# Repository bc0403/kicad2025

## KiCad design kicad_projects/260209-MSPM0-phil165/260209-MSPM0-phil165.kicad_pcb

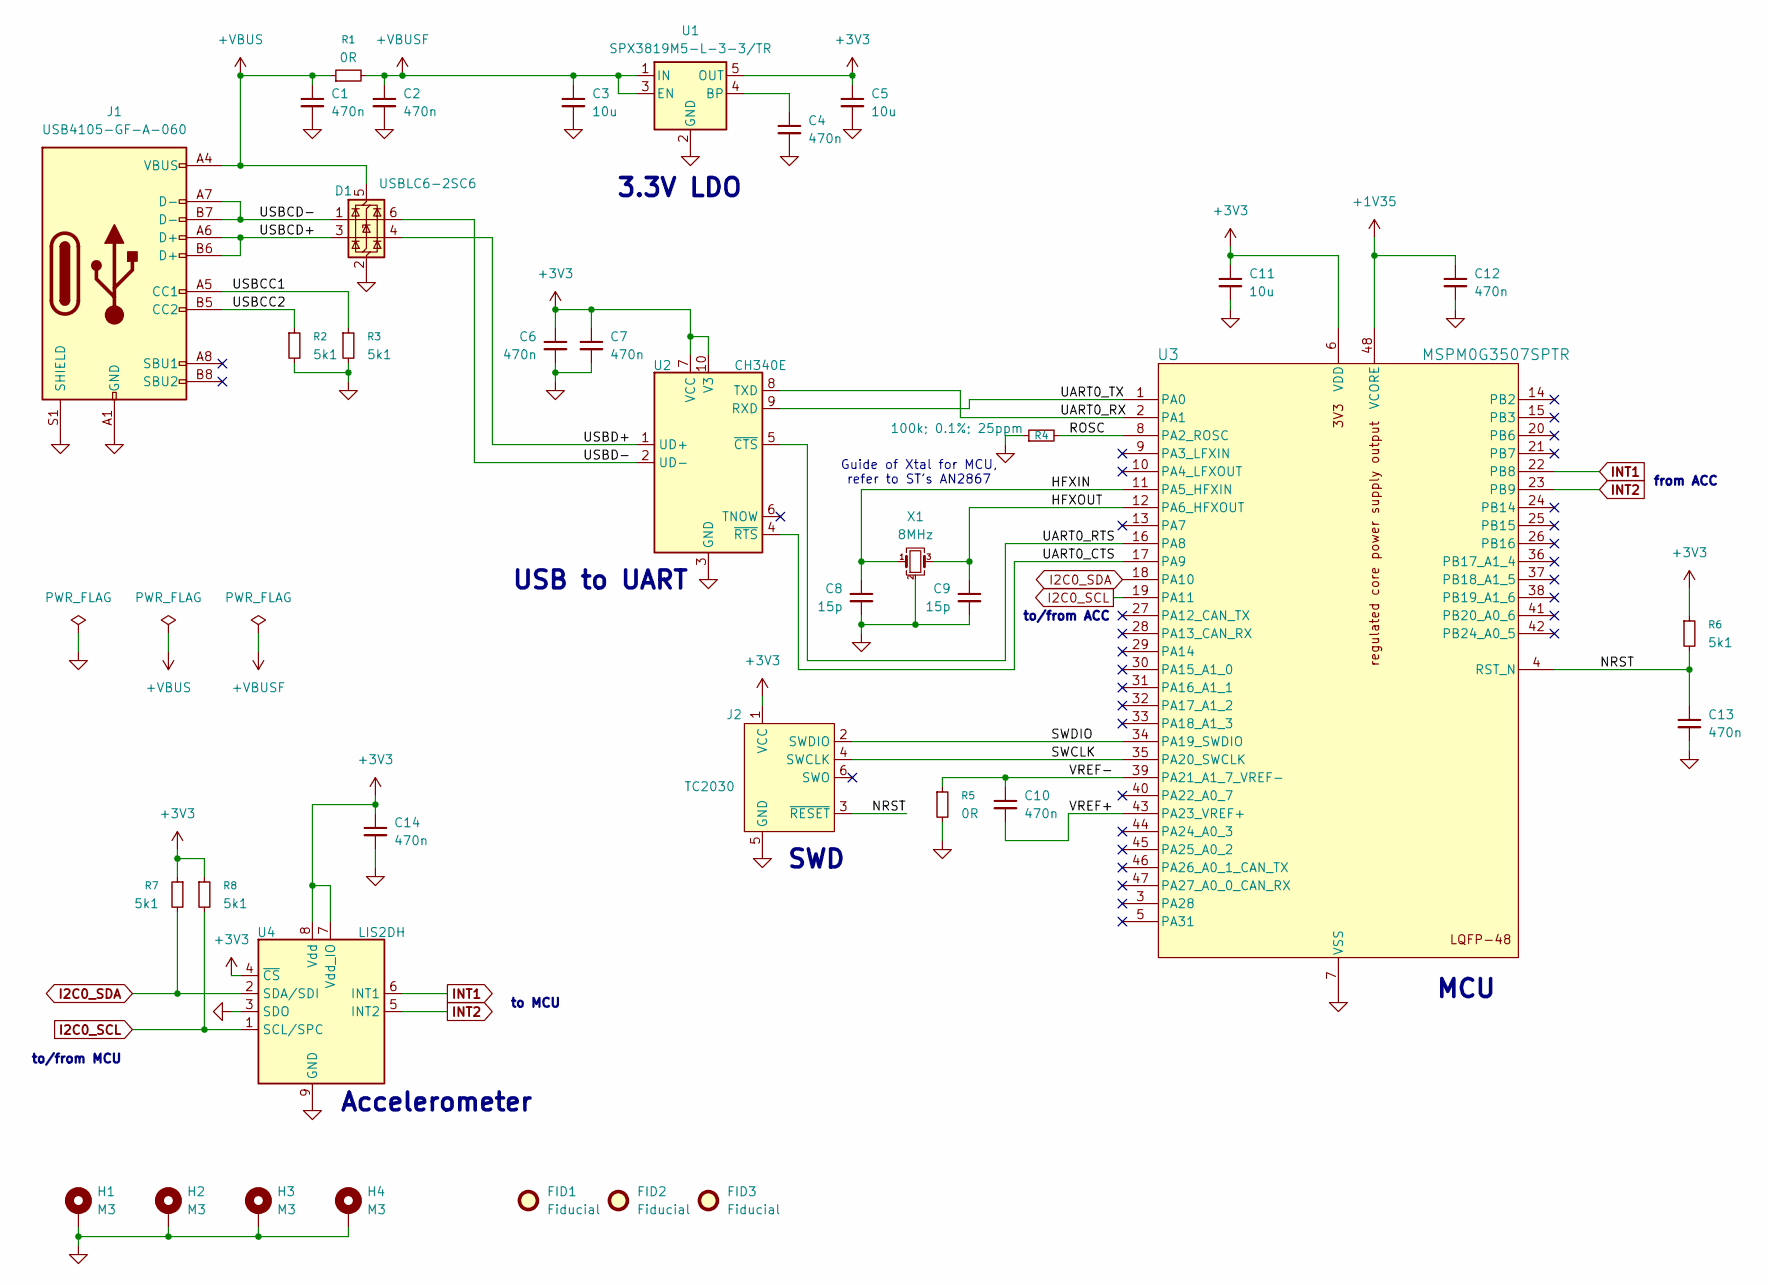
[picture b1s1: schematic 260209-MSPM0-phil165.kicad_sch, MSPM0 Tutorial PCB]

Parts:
C1, C2, C4, C6, C7, C10, C12, C13, C14: 470n; C_0603_1608Metric; MPN CL10B474KA8NNNC; Digikey 1276-2083-2-ND
C3, C5, C11: 10u; C_0805_2012Metric; MPN CL21A106KAYNNNE; Digikey 1276-2891-2-ND
C8, C9: 15p; C_0603_1608Metric; MPN CL10C150JB8NNNC; Digikey 1276-1296-2-ND
D1: USBLC6-2SC6; SOT-23-6; MPN USBLC6-2SC6; Digikey 497-5235-2-ND
FID1, FID2, FID3: Fiducial; Fiducial_1mm_Mask2mm
H1, H2, H3, H4: M3; MountingHole_3.2mm_M3_Pad_Via
J1: USB4105-GF-A-060; USB_C_Receptacle_GCT_USB4105-xx-A_16P_TopMnt_Horizontal; MPN USB4105-GF-A-060; Digikey CONN RCP USB2.0 TYP C 16P SMD RA
J2: TC2030; Tag-Connect_TC2030-IDC-FP_2x03_P1.27mm_Vertical
R1, R5: 0R; R_0603_1608Metric; MPN RC0603FR-070RL; Digikey 311-0.0HRTR-ND
R2, R3, R6, R7, R8: 5k1; R_0603_1608Metric; MPN RC0603FR-075K1L; Digikey 311-5.10KHRTR-ND
R4: 100k; 0.1%; 25ppm; R_0603_1608Metric; MPN RT0603BRD07100KL; Digikey YAG1235TR-ND
U1: SPX3819M5-L-3-3/TR; SOT-23-5; MPN SPX3819M5-L-3-3/TR; Digikey 1016-1873-2-ND
U2: CH340E; MSOP-10_3x3mm_P0.5mm; MPN CH340E; LCSC C99652
U3: MSPM0G3507SPTR; LQFP-48_7x7mm_P0.5mm; MPN MSPM0G3507SPTR; Digikey 296-MSPM0G3507SPTR-ND
U4: LIS2DH; LGA-14_2x2mm_P0.35mm_LayoutBorder3x4y; MPN LIS2DHTR; Digikey 497-13795-2-ND
X1: 8MHz; Crystal_SMD_3225-4Pin_3.2x2.5mm; MPN ECS-80-12-33-JGN-TR; Digikey 50-ECS-80-12-33-JGN-TR-ND

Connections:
+1V35: C12.1, U3.48 (VCORE)
+3V3: C5.1, C6.1, C7.1, C11.1, C14.1, J2.1 (VCC), R6.1, R7.1, R8.1, U1.5 (OUT), U2.7 (VCC), U2.10 (V3), U3.6 (VDD), U4.4 (~CS), U4.7 (Vdd_IO), U4.8 (Vdd)
+VBUS: C1.1, D1.5 (VBUS), J1.A4 (VBUS), J1.A9 (VBUS), J1.B4 (VBUS), J1.B9 (VBUS), R1.1
+VBUSF: C2.1, C3.1, R1.2, U1.1 (IN), U1.3 (EN)
/HFXIN: C8.1, U3.11 (PA5_HFXIN), X1.1
/HFXOUT: C9.1, U3.12 (PA6_HFXOUT), X1.3
/NRST: C13.1, J2.3 (~RESET), R6.2, U3.4 (RST_N)
/ROSC: R4.2, U3.8 (PA2_ROSC)
/SWCLK: J2.4 (SWCLK), U3.35 (PA20_SWCLK)
/SWDIO: J2.2 (SWDIO), U3.34 (PA19_SWDIO)
/UART0_CTS: U2.4 (~RTS), U3.17 (PA9)
/UART0_RTS: U2.5 (~CTS), U3.16 (PA8)
/UART0_RX: U2.8 (TXD), U3.2 (PA1)
/UART0_TX: U2.9 (RXD), U3.1 (PA0)
/USBCC1: J1.A5 (CC1), R3.1
/USBCC2: J1.B5 (CC2), R2.1
/USBCD+: D1.3 (I/O2), J1.A6 (D+), J1.B6 (D+)
/USBCD-: D1.1 (I/O1), J1.A7 (D-), J1.B7 (D-)
/USBD+: D1.4 (I/O2), U2.1 (UD+)
/USBD-: D1.6 (I/O1), U2.2 (UD-)
/VREF+: C10.2, U3.43 (PA23_VREF+)
/VREF-: C10.1, R5.1, U3.39 (PA21_A1_7_VREF-)
GND: C1.2, C2.2, C3.2, C4.2, C5.2, C6.2, C7.2, C8.2, C9.2, C11.2, C12.2, C13.2, C14.2, D1.2 (GND), H1.1, H2.1, H3.1, H4.1, J1.A1 (GND), J1.A12 (GND), J1.B1 (GND), J1.B12 (GND), J1.S1 (SHIELD), J2.5 (GND), R2.2, R3.2, R4.1, R5.2, U1.2 (GND), U2.3 (GND), U3.7 (VSS), U4.3 (SDO), U4.9 (GND), U4.10 (GND), U4.11 (GND), U4.12 (GND), U4.13 (GND), U4.14 (GND), X1.2 (G), X1.4 (G)
I2C0_SCL: R8.2, U3.19 (PA11), U4.1 (SCL/SPC)
I2C0_SDA: R7.2, U3.18 (PA10), U4.2 (SDA/SDI)
INT1: U3.22 (PB8), U4.6 (INT1)
INT2: U3.23 (PB9), U4.5 (INT2)
unnamed: C4.1, U1.4 (BP)

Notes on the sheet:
to/from MCU
3.3V LDO
to MCU
USB to UART
Accelerometer
to/from ACC
Guide of Xtal for MCU, refer to ST's AN2867
SWD
from ACC
MCU

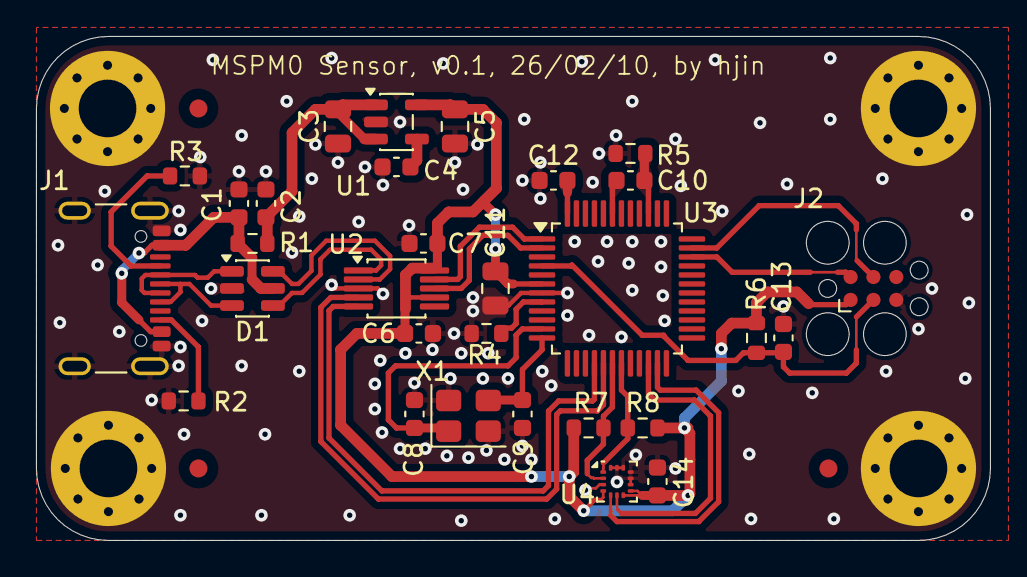
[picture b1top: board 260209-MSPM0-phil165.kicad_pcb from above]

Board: 2 copper layers, 53.0 x 28.0 mm, 37 parts (0 on the bottom side), 28 nets.

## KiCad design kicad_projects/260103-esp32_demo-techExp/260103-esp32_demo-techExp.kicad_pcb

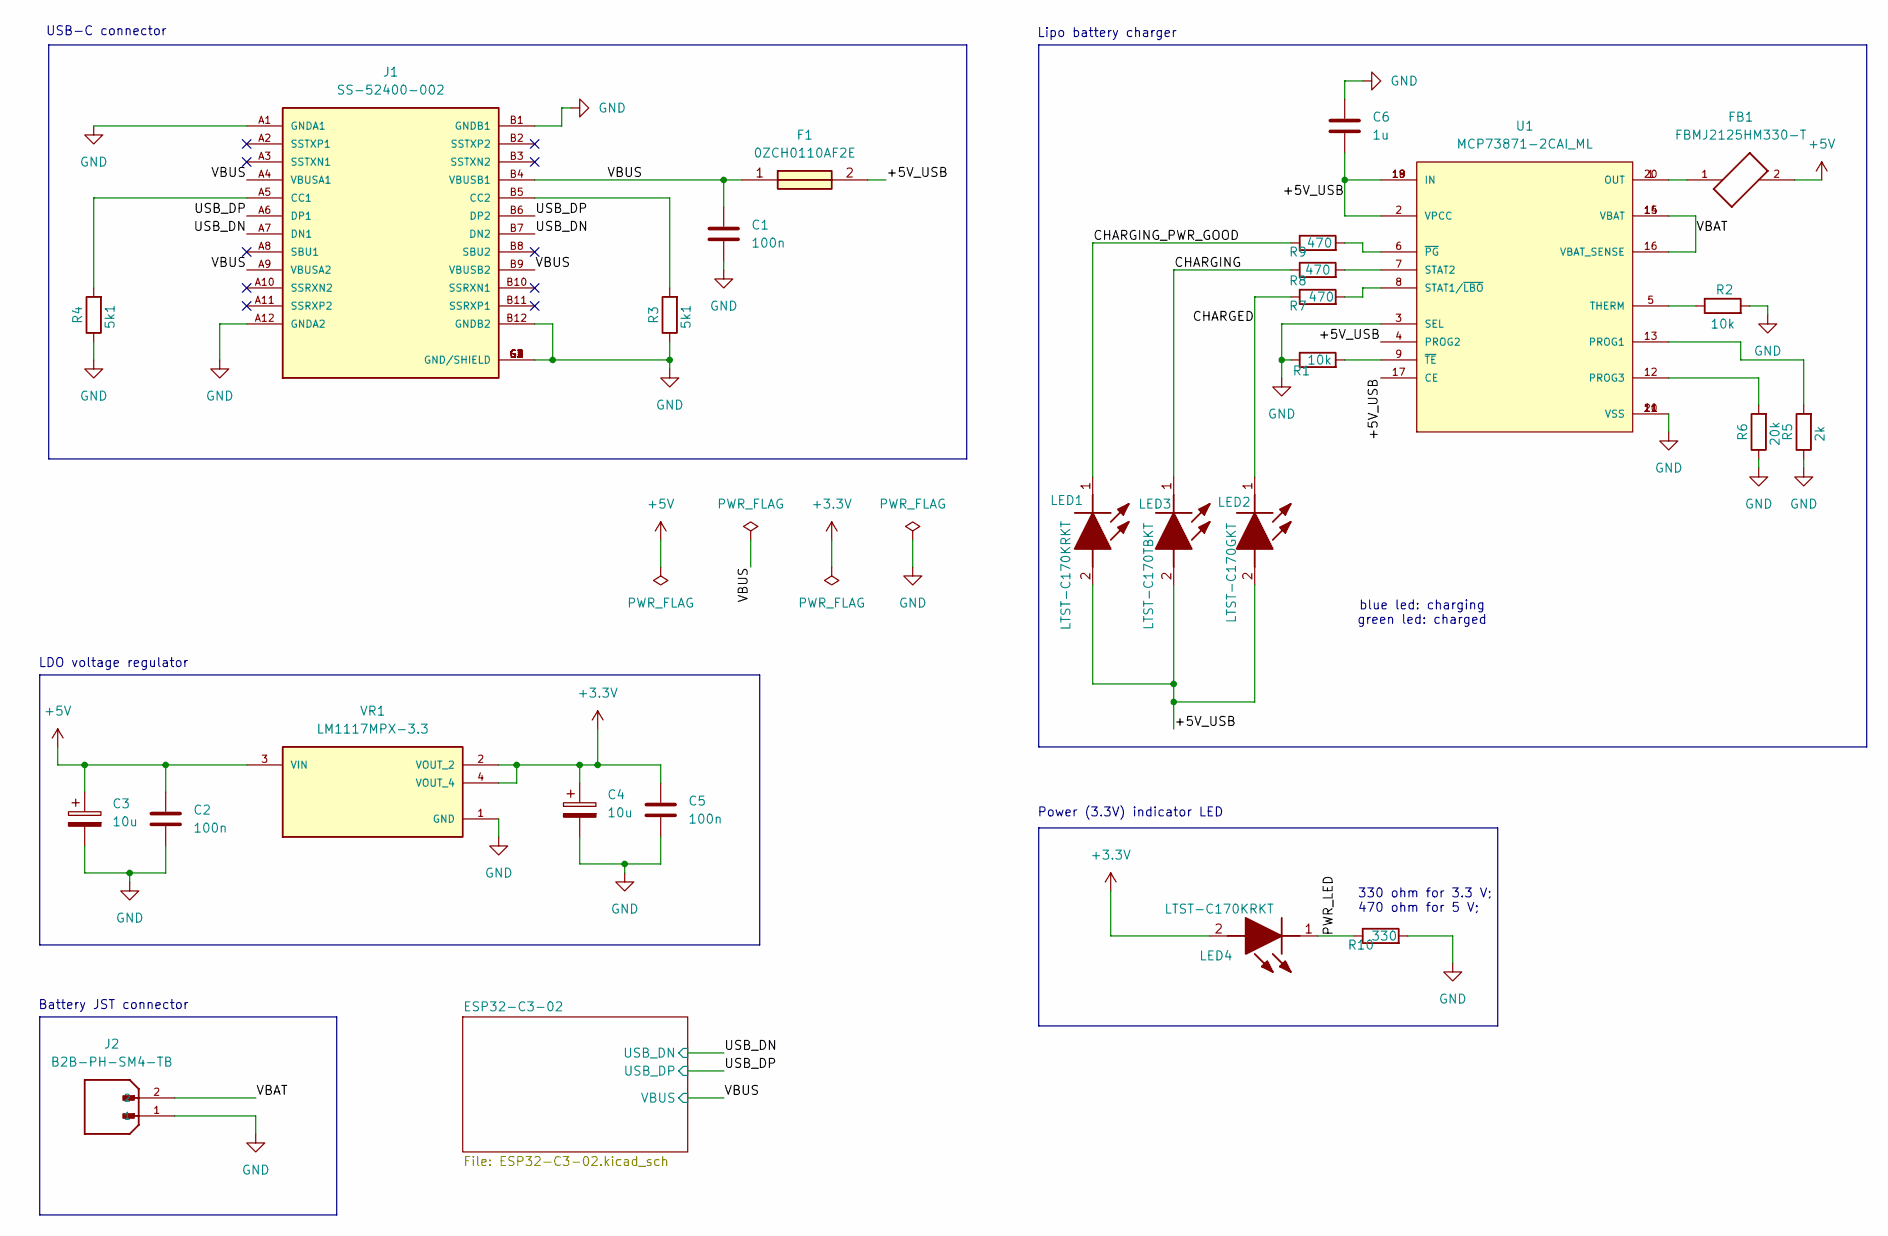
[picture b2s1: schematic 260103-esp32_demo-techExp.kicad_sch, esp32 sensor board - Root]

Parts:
C1, C2, C5: 100n; C_0805_2012Metric
C3, C4: 10u; T491A
C6: 1u; C_0805_2012Metric
F1: 0ZCH0110AF2E; FUSC3226X100N; Manufacturer_Part_Number 0ZCH0110AF2E
FB1: FBMJ2125HM330-T; BEADC2012X105N
J1: SS-52400-002; BELFUSE_SS-52400-002; PARTREV A0
J2: B2B-PH-SM4-TB; JST_B2B-PH-SM4-TB; PARTREV N/A
LED1, LED4: LTST-C170KRKT; LEDC2012X120N; Manufacturer_Part_Number LTST-C170KRKT; Mouser Part Number 859-LTST-C170KRKT
LED2: LTST-C170GKT; LEDC2012X120N; Manufacturer_Part_Number LTST-C170GKT; Mouser Part Number 859-LTST-C170GKT
LED3: LTST-C170TBKT; LEDC2012X120N; Manufacturer_Part_Number LTST-C170TBKT; Mouser Part Number 859-LTST-C170TBKT
R1, R2: 10k; R_0805_2012Metric
R3, R4: 5k1; R_0805_2012Metric
R5: 2k; R_0805_2012Metric
R6: 20k; R_0805_2012Metric
R7, R8, R9: 470; R_0805_2012Metric
R10: 330; R_0805_2012Metric
U1: MCP73871-2CAI_ML; QFN50P400X400X100-21N; PARTREV D
VR1: LM1117MPX-3.3; VREG_LM1117MPX-3.3

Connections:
+3.3V: C4.1, C5.1, LED4.2 (A), VR1.2 (VOUT_2), VR1.4 (VOUT_4); also elsewhere on the board
+5V: C2.1, C3.1, FB1.2, VR1.3 (VIN)
/+5V_USB: C6.2, F1.2, LED1.2 (A), LED2.2 (A), LED3.2 (A), U1.2 (VPCC), U1.4 (PROG2), U1.17 (CE), U1.18 (IN), U1.19 (IN)
/CHARGED: LED2.1 (K), R7.1
/CHARGING: LED3.1 (K), R8.1
/CHARGING_PWR_GOOD: LED1.1 (K), R9.1
/PWR_LED: LED4.1 (K), R10.1
/USB_DN: J1.A7 (DN1), J1.B7 (DN2); also elsewhere on the board
/USB_DP: J1.A6 (DP1), J1.B6 (DP2); also elsewhere on the board
/VBAT: J2.2, U1.14 (VBAT), U1.15 (VBAT), U1.16 (VBAT_SENSE)
/VBUS: C1.1, F1.1, J1.A4 (VBUSA1), J1.A9 (VBUSA2), J1.B4 (VBUSB1), J1.B9 (VBUSB2); also elsewhere on the board
GND: C1.2, C2.2, C3.2, C4.2, C5.2, C6.1, J1.A1 (GNDA1), J1.A12 (GNDA2), J1.B1 (GNDB1), J1.B12 (GNDB2), J1.G1 (GND/SHIELD), J1.G2 (GND/SHIELD), J1.G3 (GND/SHIELD), J1.G4 (GND/SHIELD), J1.S1 (GND/SHIELD), J1.S2 (GND/SHIELD), J1.S3 (GND/SHIELD), J1.S4 (GND/SHIELD), J2.1, R1.1, R2.2, R3.1, R4.1, R5.1, R6.1, R10.2, U1.3 (SEL), U1.10 (VSS), U1.11 (VSS), U1.21 (VSS), VR1.1 (GND); also elsewhere on the board
unnamed: FB1.1, U1.1 (OUT), U1.20 (OUT)
unnamed: J1.A5 (CC1), R4.2
unnamed: J1.B5 (CC2), R3.2
unnamed: R5.2, U1.13 (PROG1)
unnamed: R6.2, U1.12 (PROG3)
unnamed: R7.2, U1.8 (STAT1/~LBO)
unnamed: R8.2, U1.7 (STAT2)
unnamed: R2.1, U1.5 (THERM)
unnamed: R9.2, U1.6 (~PG)
unnamed: R1.2, U1.9 (~TE)

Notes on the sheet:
Lipo battery charger
330 ohm for 3.3 V; 470 ohm for 5 V;
Battery JST connector
blue led: charging green led: charged
LDO voltage regulator
Power (3.3V) indicator LED
USB-C connector

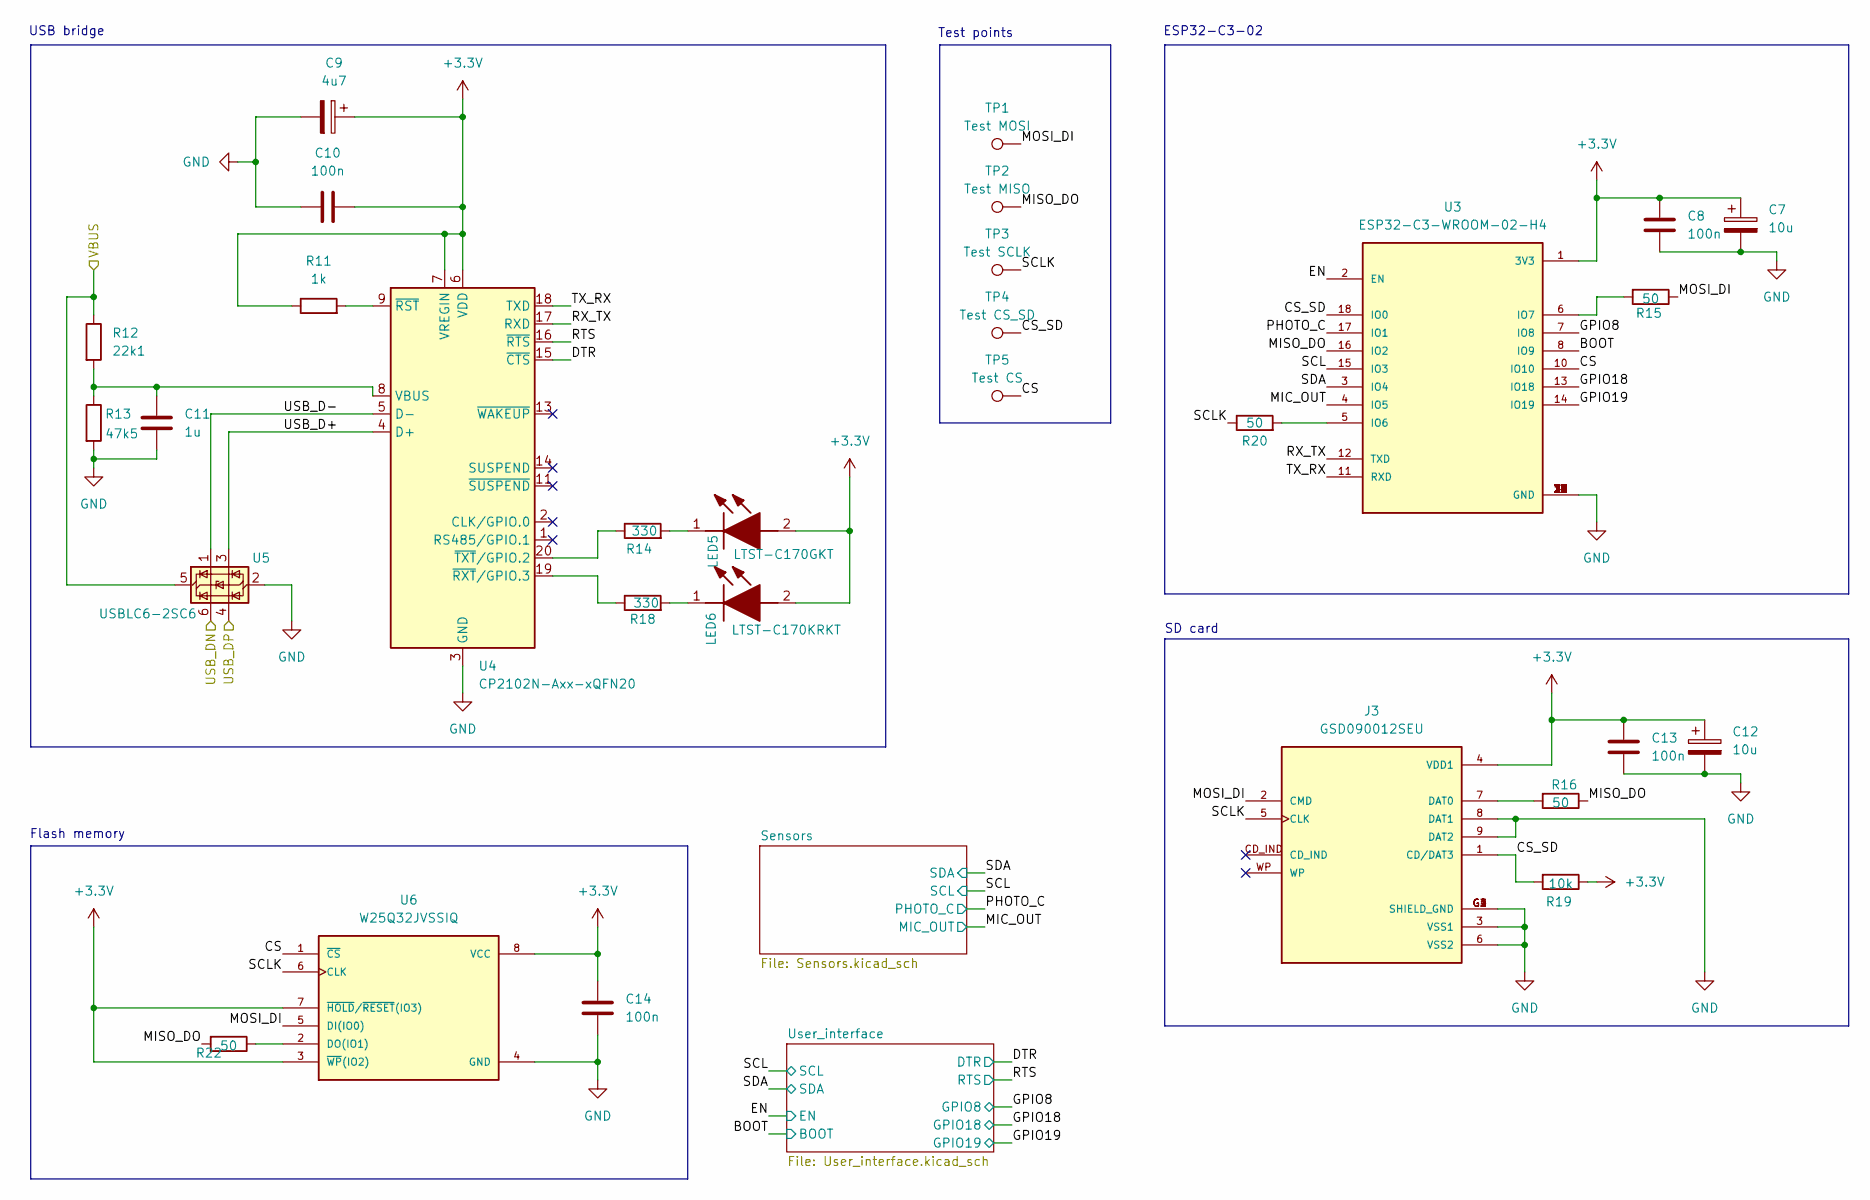
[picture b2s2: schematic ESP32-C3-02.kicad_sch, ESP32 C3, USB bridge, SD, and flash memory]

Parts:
C7, C12: 10u; T491A
C8, C10, C13, C14: 100n; C_0805_2012Metric
C9: 4u7; T491A
C11: 1u; C_0805_2012Metric
J3: GSD090012SEU; AMPHENOL_GSD090012SEU; PARTREV E
LED5: LTST-C170GKT; LEDC2012X120N; Manufacturer_Part_Number LTST-C170GKT; Mouser Part Number 859-LTST-C170GKT
LED6: LTST-C170KRKT; LEDC2012X120N; Manufacturer_Part_Number LTST-C170KRKT; Mouser Part Number 859-LTST-C170KRKT
R11: 1k; R_0805_2012Metric
R12: 22k1; R_0805_2012Metric
R13: 47k5; R_0805_2012Metric
R14, R18: 330; R_0805_2012Metric
R15, R16, R20, R22: 50; R_0805_2012Metric
R19: 10k; R_0805_2012Metric
TP1: Test MOSI; TestPoint_Pad_D1.0mm
TP2: Test MISO; TestPoint_Pad_D1.0mm
TP3: Test SCLK; TestPoint_Pad_D1.0mm
TP4: Test CS_SD; TestPoint_Pad_D1.0mm
TP5: Test CS; TestPoint_Pad_D1.0mm
U3: ESP32-C3-WROOM-02-H4; MODULE_ESP32-C3-WROOM-02-H4
U4: CP2102N-Axx-xQFN20; SiliconLabs_QFN-20-1EP_3x3mm_P0.5mm_EP1.8x1.8mm
U5: USBLC6-2SC6; SOT-23-6
U6: W25Q32JVSSIQ; SOIC127P790X216-8N; M_PART_NUMBER W25QXX

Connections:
+3.3V: C7.1, C8.1, C9.1, C10.2, C12.1, C13.1, C14.1, J3.4 (VDD1), LED5.2 (A), LED6.2 (A), R11.1, R19.1, U3.1 (3V3), U4.6 (VDD), U4.7 (VREGIN), U6.3 (~WP(IO2)), U6.7 (~HOLD/~RESET(IO3)), U6.8 (VCC); also elsewhere on the board
/ESP32-C3-02/BOOT: U3.8 (IO9); also elsewhere on the board
/ESP32-C3-02/CS: TP5.1, U3.10 (IO10), U6.1 (~CS)
/ESP32-C3-02/CS_SD: J3.1 (CD/DAT3), R19.2, TP4.1, U3.18 (IO0)
/ESP32-C3-02/DTR: U4.15 (~CTS); also elsewhere on the board
/ESP32-C3-02/EN: U3.2 (EN); also elsewhere on the board
/ESP32-C3-02/GPIO8: U3.7 (IO8); also elsewhere on the board
/ESP32-C3-02/GPIO18: U3.13 (IO18); also elsewhere on the board
/ESP32-C3-02/GPIO19: U3.14 (IO19); also elsewhere on the board
/ESP32-C3-02/MIC_OUT: U3.4 (IO5); also elsewhere on the board
/ESP32-C3-02/MISO_DO: R16.1, R22.2, TP2.1, U3.16 (IO2)
/ESP32-C3-02/MOSI_DI: J3.2 (CMD), R15.1, TP1.1, U6.5 (DI(IO0))
/ESP32-C3-02/PHOTO_C: U3.17 (IO1); also elsewhere on the board
/ESP32-C3-02/RTS: U4.16 (~RTS); also elsewhere on the board
/ESP32-C3-02/RX_TX: U3.12 (TXD), U4.17 (RXD)
/ESP32-C3-02/SCL: U3.15 (IO3); also elsewhere on the board
/ESP32-C3-02/SCLK: J3.5 (CLK), R20.1, TP3.1, U6.6 (CLK)
/ESP32-C3-02/SDA: U3.3 (IO4); also elsewhere on the board
/ESP32-C3-02/TX_RX: U3.11 (RXD), U4.18 (TXD)
/ESP32-C3-02/USB_D+: U4.4 (D+), U5.3 (I/O2)
/ESP32-C3-02/USB_D-: U4.5 (D-), U5.1 (I/O1)
/USB_DN: U5.6 (I/O1); also elsewhere on the board
/USB_DP: U5.4 (I/O2); also elsewhere on the board
/VBUS: R12.1, U5.5 (VBUS); also elsewhere on the board
GND: C7.2, C8.2, C9.2, C10.1, C11.2, C12.2, C13.2, C14.2, J3.3 (VSS1), J3.6 (VSS2), J3.8 (DAT1), J3.9 (DAT2), J3.G1 (SHIELD_GND), J3.G2 (SHIELD_GND), J3.G3 (SHIELD_GND), J3.G4 (SHIELD_GND), R13.2, U3.9 (GND), U3.19 (GND), U3.20 (GND), U3.21 (GND), U3.22 (GND), U3.23 (GND), U3.24 (GND), U3.25 (GND), U3.26 (GND), U3.27 (GND), U3.28 (GND), U3.29 (GND), U3.30 (GND), U3.31 (GND), U3.32 (GND), U3.33 (GND), U3.34 (GND), U3.35 (GND), U3.36 (GND), U3.37 (GND), U3.38 (GND), U3.39 (GND), U4.3 (GND), U4.12 (GND), U4.21 (GND), U5.2 (GND), U6.4 (GND); also elsewhere on the board
unnamed: J3.7 (DAT0), R16.2
unnamed: LED5.1 (K), R14.2
unnamed: LED6.1 (K), R18.2
unnamed: R20.2, U3.5 (IO6)
unnamed: R15.2, U3.6 (IO7)
unnamed: C11.1, R12.2, R13.1, U4.8 (VBUS)
unnamed: R11.2, U4.9 (~RST)
unnamed: R18.1, U4.19 (~RXT/GPIO.3)
unnamed: R14.1, U4.20 (~TXT/GPIO.2)
unnamed: R22.1, U6.2 (DO(IO1))

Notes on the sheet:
Test points
ESP32-C3-02
USB bridge
Flash memory
SD card

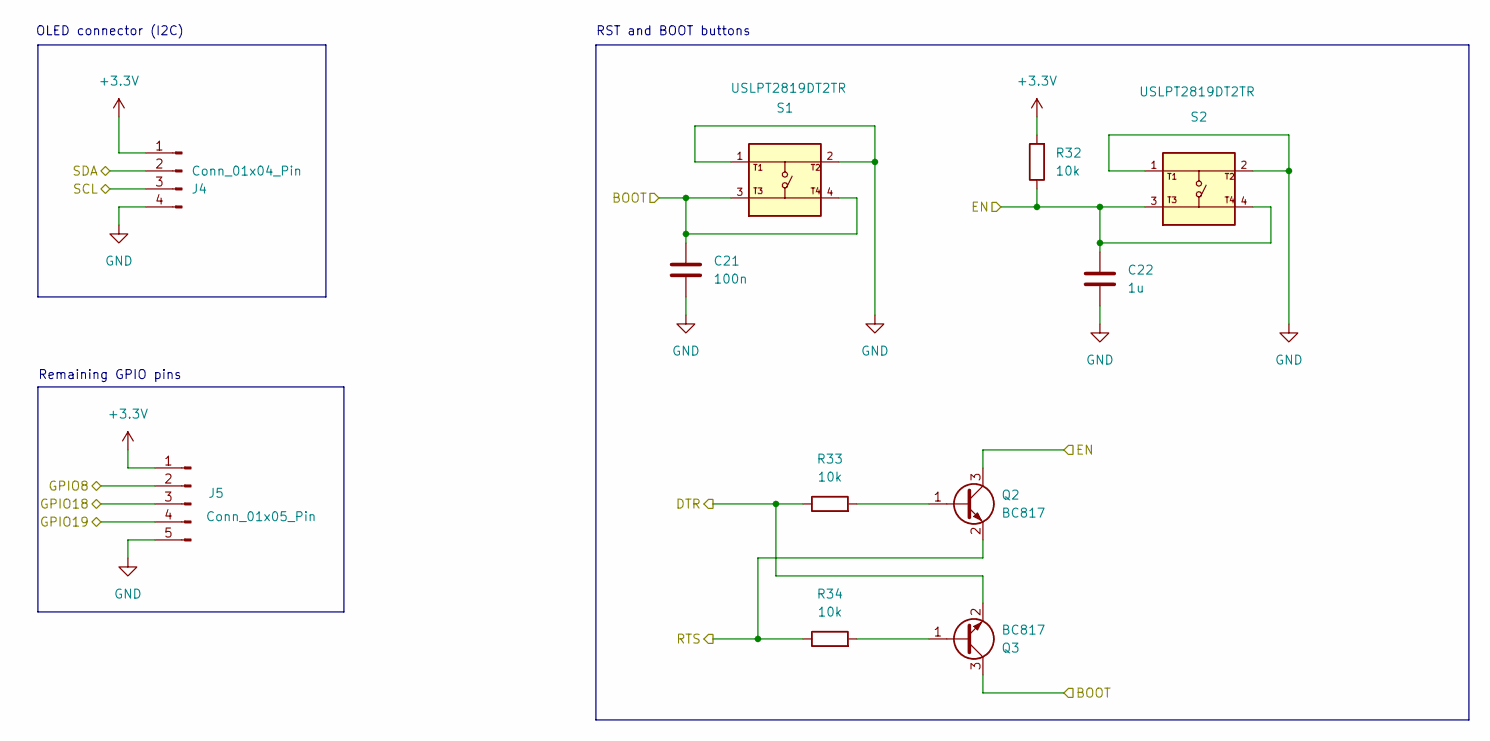
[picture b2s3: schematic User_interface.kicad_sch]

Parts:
C21: 100n; C_0805_2012Metric
C22: 1u; C_0805_2012Metric
J4: Conn_01x04_Pin; PinHeader_1x04_P2.54mm_Vertical
J5: Conn_01x05_Pin; PinHeader_1x05_P2.54mm_Vertical
Q2, Q3: BC817; SOT-23
R32, R33, R34: 10k; R_0805_2012Metric
S1, S2: USLPT2819DT2TR; SW_USLPT2819DT2TR; PARTREV P

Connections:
+3.3V: J4.1, J5.1, R32.2; also elsewhere on the board
/ESP32-C3-02/BOOT: C21.1, Q3.3 (C), S1.3, S1.4; also elsewhere on the board
/ESP32-C3-02/DTR: Q3.2 (E), R33.1; also elsewhere on the board
/ESP32-C3-02/EN: C22.1, Q2.3 (C), R32.1, S2.3, S2.4; also elsewhere on the board
/ESP32-C3-02/GPIO8: J5.2; also elsewhere on the board
/ESP32-C3-02/GPIO18: J5.3; also elsewhere on the board
/ESP32-C3-02/GPIO19: J5.4; also elsewhere on the board
/ESP32-C3-02/RTS: Q2.2 (E), R34.1; also elsewhere on the board
/ESP32-C3-02/SCL: J4.3; also elsewhere on the board
/ESP32-C3-02/SDA: J4.2; also elsewhere on the board
GND: C21.2, C22.2, J4.4, J5.5, S1.1, S1.2, S2.1, S2.2; also elsewhere on the board
unnamed: Q2.1 (B), R33.2
unnamed: Q3.1 (B), R34.2

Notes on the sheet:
RST and BOOT buttons
Remaining GPIO pins
OLED connector (I2C)

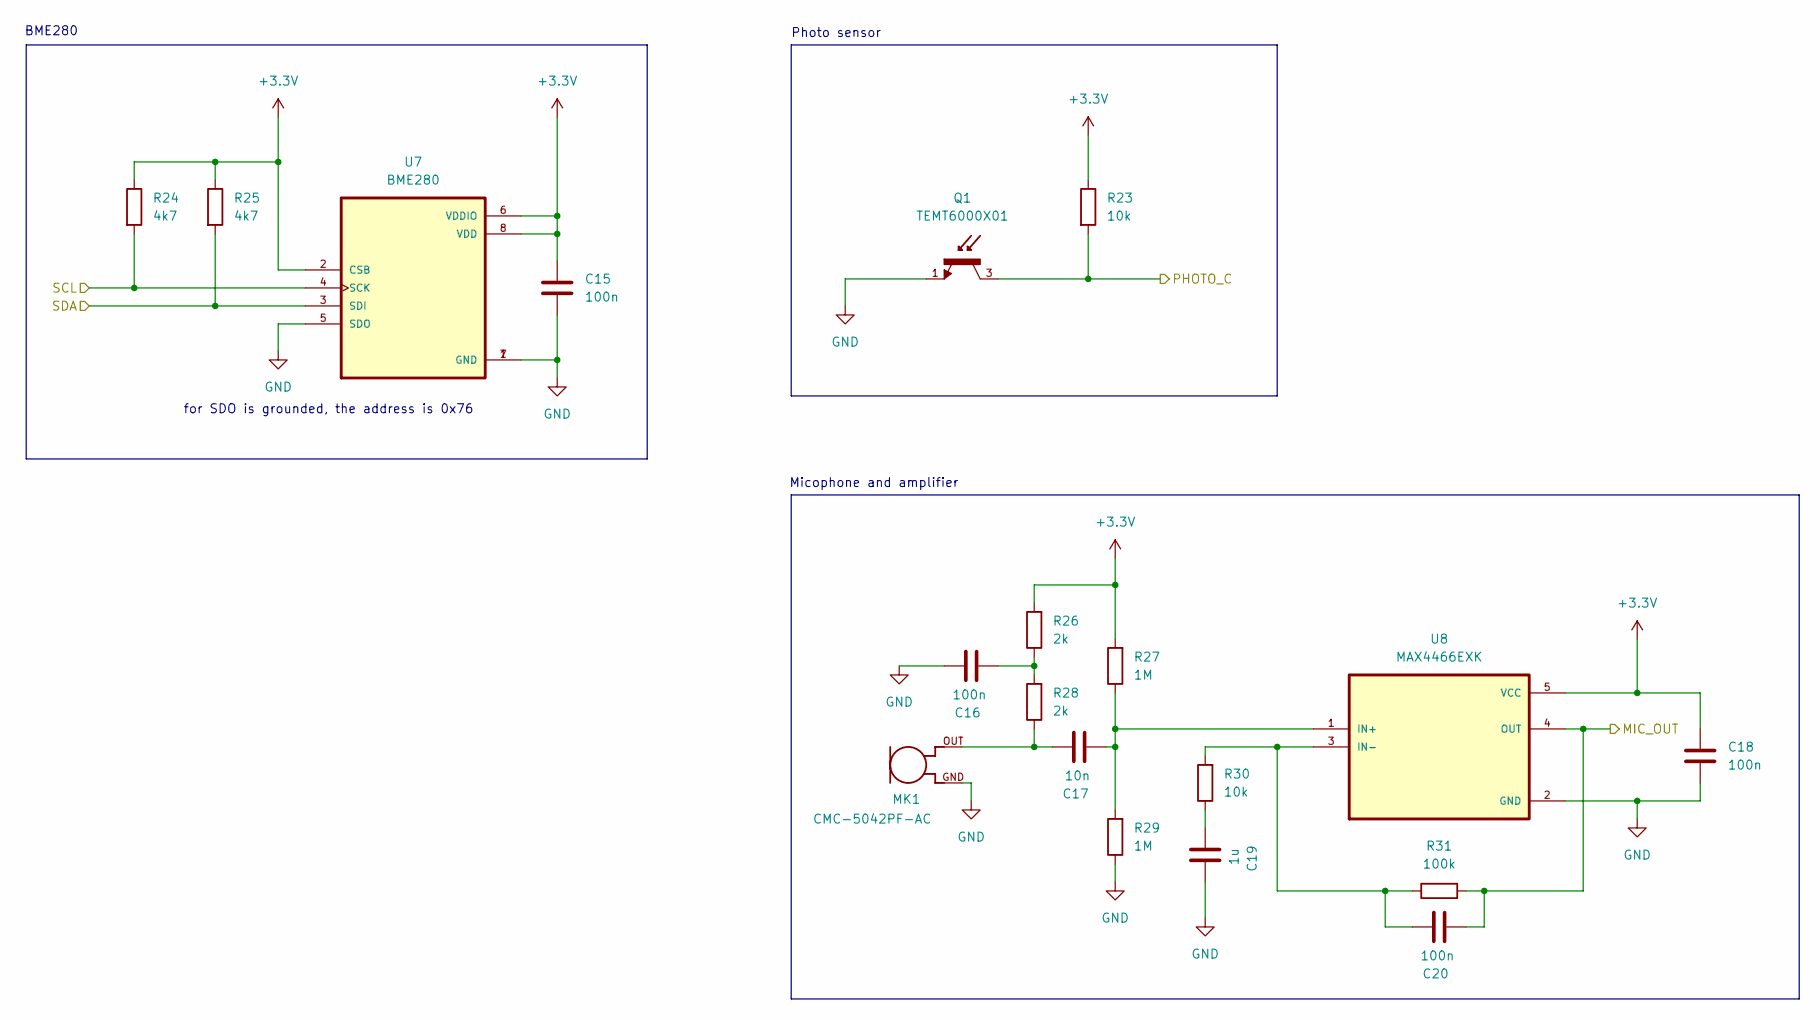
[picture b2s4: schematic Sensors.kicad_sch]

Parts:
C15, C16, C18, C20: 100n; C_0805_2012Metric
C17: 10n; C_0805_2012Metric
C19: 1u; C_0805_2012Metric
MK1: CMC-5042PF-AC; CUI_CMC-5042PF-AC
Q1: TEMT6000X01; TRANS_TEMT6000X01; PARTREV 1.9
R23, R30: 10k; R_0805_2012Metric
R24, R25: 4k7; R_0805_2012Metric
R26, R28: 2k; R_0805_2012Metric
R27, R29: 1M; R_0805_2012Metric
R31: 100k; R_0805_2012Metric
U7: BME280; PSON65P250X250X100-8N
U8: MAX4466EXK; SOT65P210X110-5N

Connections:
+3.3V: C15.1, C18.1, R23.1, R24.1, R25.1, R26.2, R27.2, U7.2 (CSB), U7.6 (VDDIO), U7.8 (VDD), U8.5 (VCC); also elsewhere on the board
/ESP32-C3-02/MIC_OUT: C20.2, R31.2, U8.4 (OUT); also elsewhere on the board
/ESP32-C3-02/PHOTO_C: Q1.3, R23.2; also elsewhere on the board
/ESP32-C3-02/SCL: R24.2, U7.4 (SCK); also elsewhere on the board
/ESP32-C3-02/SDA: R25.2, U7.3 (SDI); also elsewhere on the board
GND: C15.2, C16.1, C18.2, C19.1, MK1.GND, Q1.1, R29.1, U7.1 (GND), U7.5 (SDO), U7.7 (GND), U8.2 (GND); also elsewhere on the board
unnamed: C16.2, R26.1, R28.2
unnamed: C17.1, MK1.OUT, R28.1
unnamed: C19.2, R30.1
unnamed: C17.2, R27.1, R29.2, U8.1 (IN+)
unnamed: C20.1, R30.2, R31.1, U8.3 (IN-)

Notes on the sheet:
BME280
for SDO is grounded, the address is 0x76
Micophone and amplifier
Photo sensor

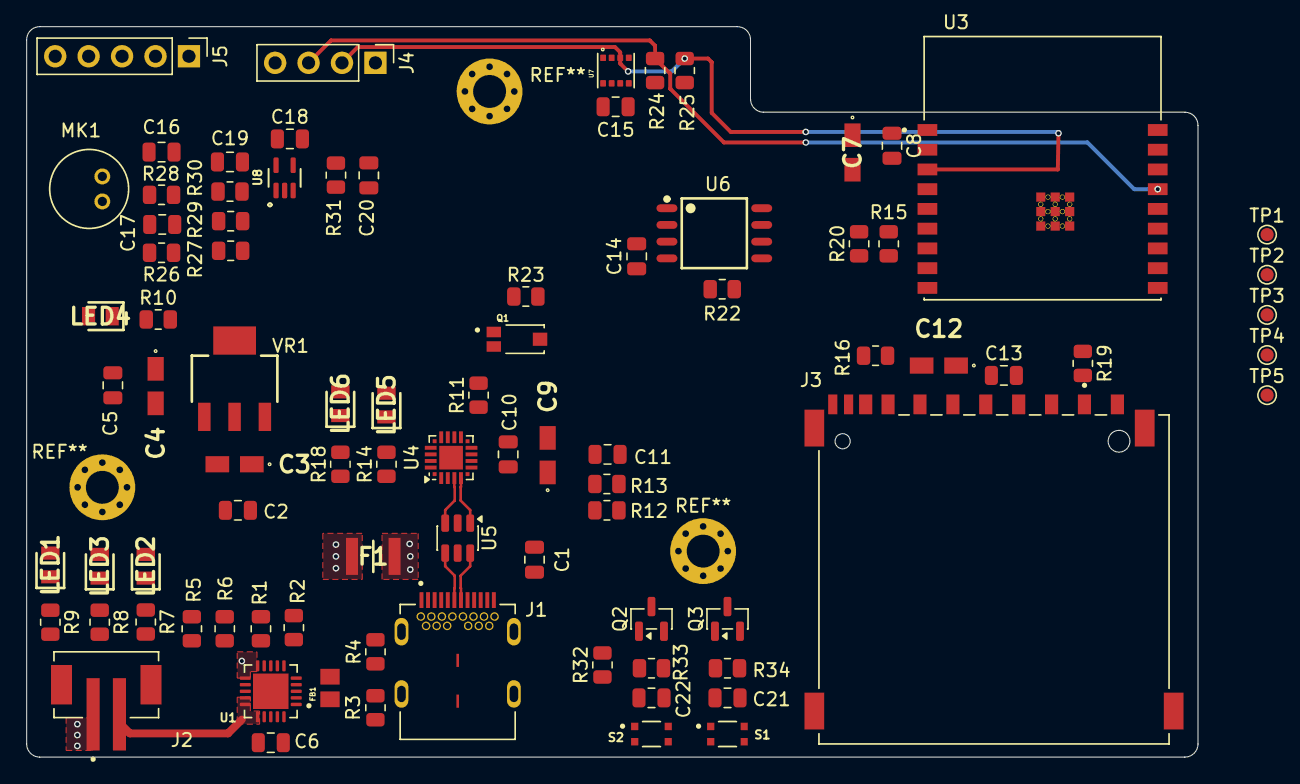
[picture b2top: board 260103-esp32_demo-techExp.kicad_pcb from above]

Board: 4 copper layers, 89.0 x 55.5 mm, 86 parts (0 on the bottom side), 59 nets.

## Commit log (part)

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2025-10-26 regular
2026-01-03 track csv files
2026-01-03 init
2026-01-10 using claude
